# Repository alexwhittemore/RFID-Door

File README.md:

RFID Door Lock
==============

This project centers around a [Parallax RFID reader](http://www.parallax.com/tabid/768/ProductID/114/Default.aspx) and an Arduino for reading 125khz RFID tags as a means of authentication for opening a deadbolt. The main PCB holds the barebones Arduino-compatible clone, a socket for a Digi Xbee module for communication with a home automation network or a computer, and power circuitry. It has connectors for the RFID module, a standard hobby servo to actuate the deadbolt, and a magnetic reed switch to sense whether or not the door is presently closed. It also has a header which breaks out all power connections, such that external 5V and 3.3V sources can be used.

RFID Reader
-----------

The Parallax RFID Reader above from Grand Idea Studio and Parallax is used. Both SOUT and /ENABLE are connected to the Arduino, and it is intended that a software serial port will be used (since the hardware serial is used elsewhere for communication and programming). Given this configuration, the RFID header is pin-compatible with the [new RFID reader/writer from Parallax](http://www.parallax.com/Store/Accessories/CommunicationRF/tabid/161/ProductID/688/List/0/Default.aspx?SortField=ProductName,ProductName) should that be desired in the future.

Arduino
-------

A barebones Arduino is implemented with a PDIP AVR socket (ATMega8/168/328 compatible) and an external 16MHz crystal. Arduino pins 0,1 are used for a hardware UART connection to the Xbee module. Pins 2,3 are connected to RFID SOUT and /ENABLE, respectively, usable either as GPIO or software serial. Pin 5 is used to drive the servo motor signal. AD 0 is used to sense the door open magnetic reed switch. Pull up and pull down resistor footprints are included, to be populated in accordance with the use of a normally open or normally closed reed switch. 

Additionally, a reset switch and an ISP programming header are included for users who may wish to program the chip either without the Arduino environment or simply without removing the chip from the board.

Xbee
----

A socket is included for use with a Digi Xbee module. These should all be pin-compatible across series 1/2/pro units as well as 2.4GHz/900MHz, and only the power, reset, and serial pins are utilzed. Installing this optional module allows for remote programming (I think?) as well as communication with the rest of a home automation network or a central computer. Ideas for this feature are: dynamic updating of the access list, access logging, internet-based access interface (unlock the door from your smart phone!). A reset button for the Xbee is also implemented, as is necessary for remote updating.

Level Translation
-----------------

The Xbee module is 3.3v and the Arduino is 5v, so level translation on the UART lines is necessary. The method used in the Xbee shield for Arduino is a series 10kOhm resistor on the Arduino Tx/Xbee Rx line such that the ESD diodes in the Xbee aren't overwhelmed with 20mA out of the Arduino. There is no translation on the Xbee Tx/Arduino Rx, with the expectation that 3.3v will be sufficient for a logic 'High' on the Arduino. This scheme may be used for parts count/cost reduction by solder bridging SJ1 and populating R3.

Alternately, footprints are included for On Semi MC74VHC1GT126 level non-inverting buffers. These will accurately translate 3.3V inputs to 5V outputs and vice-versa, where any input 0-10V is acceptable and 'High' output = Vdd. Populate these and leave SJ1 and R3 unbridged/unpopulated for full level translation.

Finally, headers on both input and output sides of level translation are included for ease of debugging.

Power
-----

Regulators are included with appropriate bypassing for 5V and 3.3V supplies. They are cascaded - a Vin pin is provided to supply power to be regulated down to 5V, then the 3.3V regulator takes its input from this 5V line:

Vin->`7805 Regulator`--5V+USB-->`REG103`-->3.3V

Therefore, the 5V regulator may be populated, and simply won't be used if Vin isn't supplied. However, if both external 5V and 3.3V supplies are used, the 3.3V regulator MUST be unpopulated! A USB Mini-B connector is also provided to optionally supply 5V power. Note that there is NO protection of ANY kind - this is intended only for use with dumb wall chargers or CAREFUL use supplying power from a computer. That is, the 5v regulator MUST NOT have power to it, or there could be damage!

Additionally, a REG103 from Burr-Brown (TI) is used as the 3.3V regulator. It's not a conventional part in the hobbyist spectrum (It's not used by Sparkfun/Dangerous Prototypes/OpenPilot/anyone else) - I just happened to have some. But they're inexpensive and highly available on Digikey and Mouser.

Software
--------

I haven't written it yet. But if you get to it before I do, it's a pretty standard mishmash of the SoftwareSerial library, some demo code for the RFID reader, and standard UART for the Xbee.

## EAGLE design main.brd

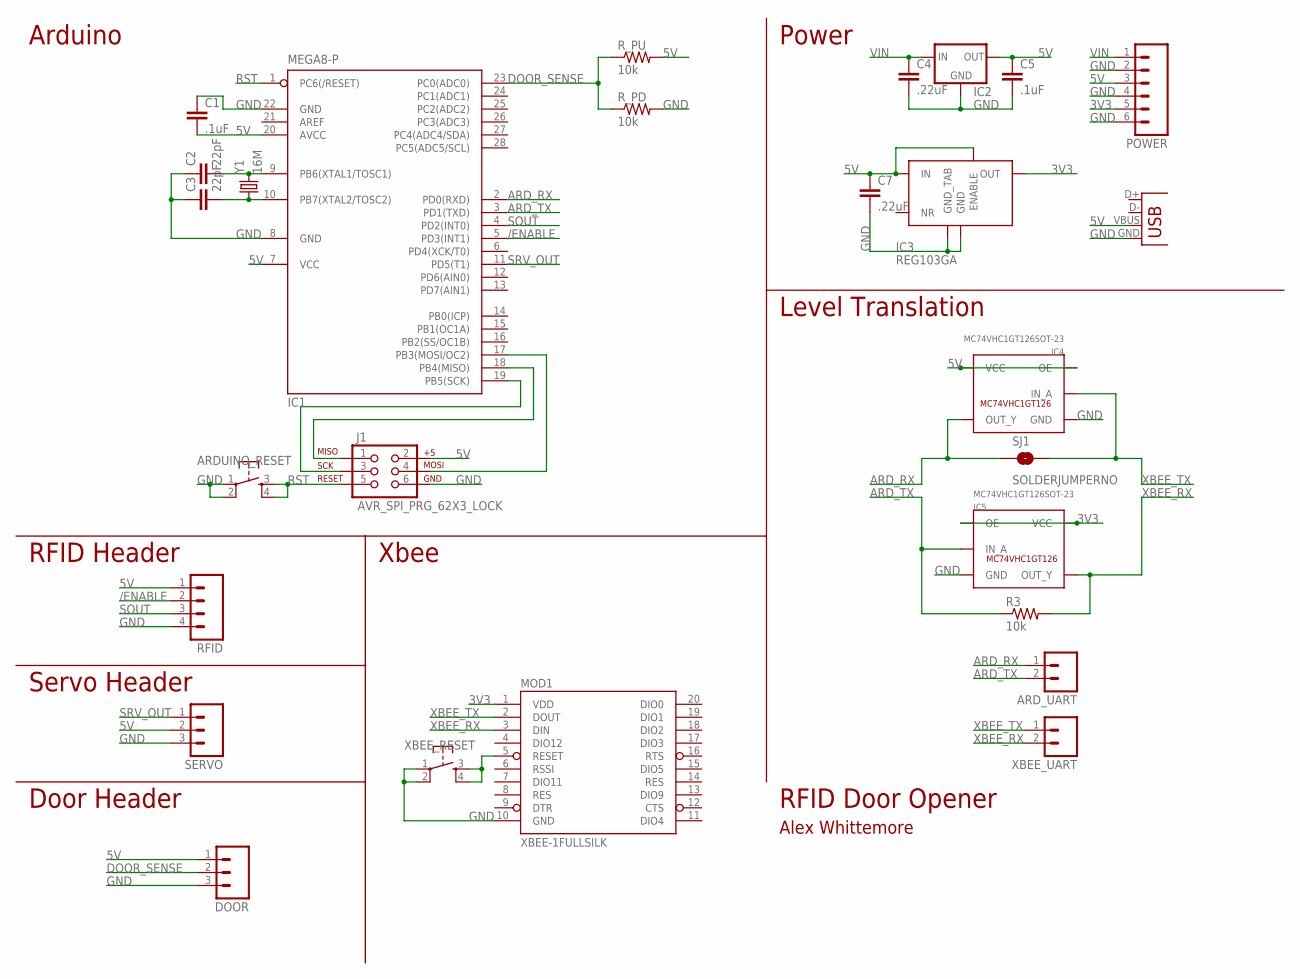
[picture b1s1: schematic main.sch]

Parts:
ARDUINO_RESET: TAC_SWITCHPTH; TACTILE-PTH
ARD_UART: M02LOCK_LONGPADS; 1X02_LOCK_LONGPADS
C1, C5: .1uF; 0805
C2, C3: 22pF; 0805
C4, C7: .22uF; 0805
DOOR: M03LOCK; 1X03_LOCK
IC1: MEGA8-P; DIL28-3
IC2: V_REG_78XX-TO-220; TO-220-ALT
IC3: REG103GA; SOT223-5
IC4, IC5: MC74VHC1GT126SOT-23; SOT23-5L
J1: AVR_SPI_PRG_62X3_LOCK; 2X3_LOCK
MOD1: XBEE-1FULLSILK; XBEE
POWER: M06LOCK; 1X06_LOCK
R3: 10k; 0805
RFID: M04LOCK_LONGPADS; 1X04_LOCK_LONGPADS
R_PD: 10k; 0805
R_PU: 10k; 0805
SERVO: M03LOCK; 1X03_LOCK
SJ1: SOLDERJUMPERNO; SJ_2S-NO
X1: USB-SMD-NS; USB-MINIB-NOSTOP
XBEE_RESET: TAC_SWITCHPTH; TACTILE-PTH
XBEE_UART: M02LOCK_LONGPADS; 1X02_LOCK_LONGPADS
Y1: 16M; HC49UP

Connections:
3V3: IC3.2 (OUT), IC5.1 (OE), IC5.5 (VCC), MOD1.1 (VDD), POWER.5
5V: C1.2, C5.1, C7.1, DOOR.1, IC1.7 (VCC), IC1.20 (AVCC), IC2.OUT, IC3.1 (IN), IC3.5 (ENABLE), IC4.1 (OE), IC4.5 (VCC), J1.2, POWER.3, RFID.1, R_PU.2, SERVO.2, X1.VBUS
/ENABLE: IC1.5 (PD3(INT1)), RFID.2
ARD_RX: ARD_UART.1, IC1.2 (PD0(RXD)), IC4.4 (OUT_Y), SJ1.1
ARD_TX: ARD_UART.2, IC1.3 (PD1(TXD)), IC5.2 (IN_A), R3.1
DOOR_SENSE: DOOR.2, IC1.23 (PC0(ADC0)), R_PD.1, R_PU.1
GND: ARDUINO_RESET.1, ARDUINO_RESET.2, C1.1, C2.1, C3.1, C4.2, C5.2, C7.2, DOOR.3, IC1.8 (GND), IC1.22 (GND), IC2.GND, IC3.3 (GND), IC3.TAB (GND_TAB), IC4.3 (GND), IC5.3 (GND), J1.6, MOD1.10 (GND), POWER.2, POWER.4, POWER.6, RFID.4, R_PD.2, SERVO.3, X1.GND, XBEE_RESET.1, XBEE_RESET.2
ISP_MISO: IC1.18 (PB4(MISO)), J1.1
ISP_MOSI: IC1.17 (PB3(MOSI/OC2)), J1.4
ISP_SCK: IC1.19 (PB5(SCK)), J1.3
unnamed: C2.2, IC1.9 (PB6(XTAL1/TOSC1)), Y1.2
unnamed: C3.2, IC1.10 (PB7(XTAL2/TOSC2)), Y1.1
RST: ARDUINO_RESET.3, ARDUINO_RESET.4, IC1.1 (PC6(/RESET)), J1.5
SOUT: IC1.4 (PD2(INT0)), RFID.3
SRV_OUT: IC1.11 (PD5(T1)), SERVO.1
VIN: C4.1, IC2.IN, POWER.1
XBEE_RST: MOD1.5 (RESET), XBEE_RESET.3, XBEE_RESET.4
XBEE_RX: IC5.4 (OUT_Y), MOD1.3 (DIN), R3.2, XBEE_UART.2
XBEE_TX: IC4.2 (IN_A), MOD1.2 (DOUT), SJ1.2, XBEE_UART.1

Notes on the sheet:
Level Translation
Power
Arduino
Xbee
RFID Header
Servo Header
Door Header
RFID Door Opener
Alex Whittemore

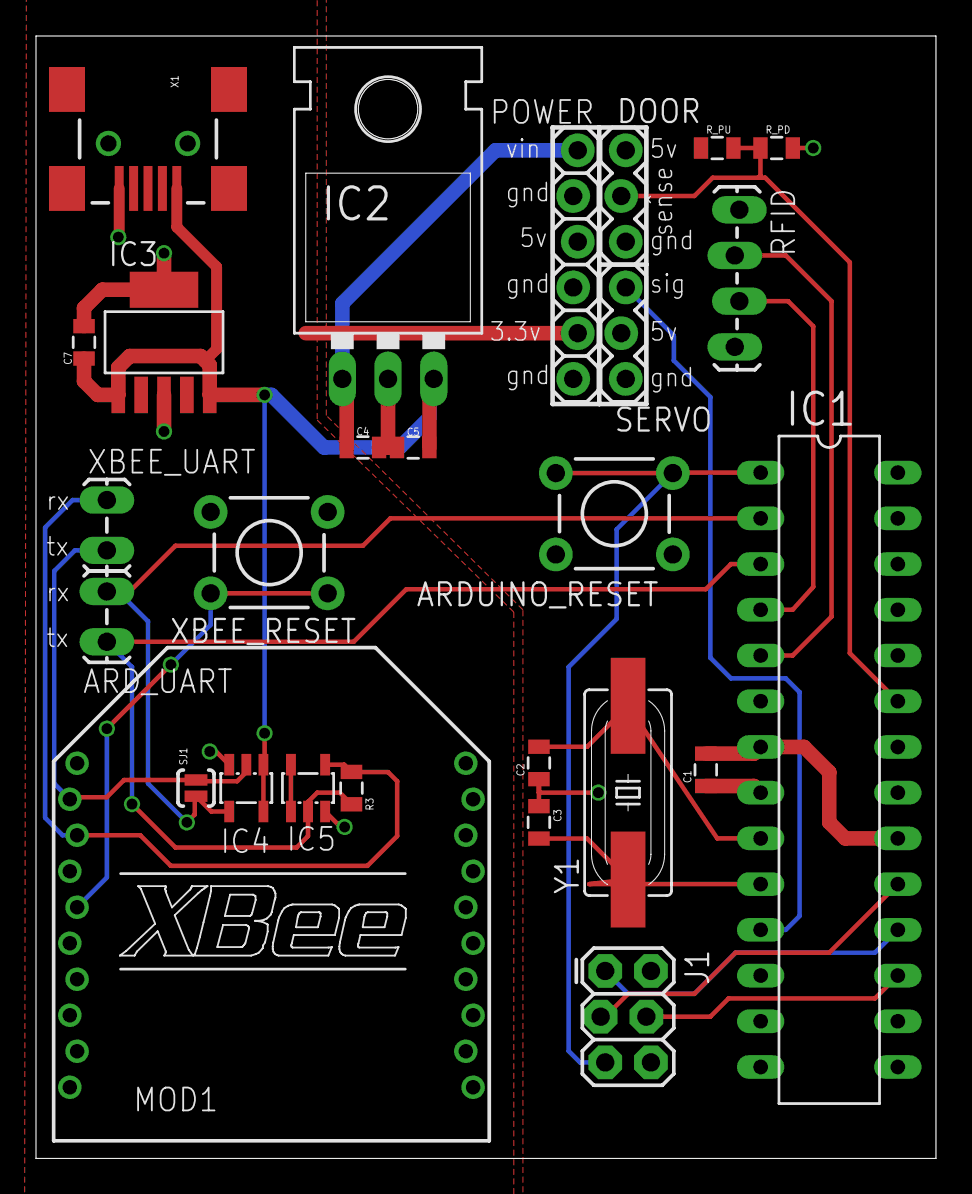
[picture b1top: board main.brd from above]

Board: 2 copper layers, 50.0 x 62.4 mm, 27 parts (0 on the bottom side), 19 nets.

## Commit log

2011-11-30 Initial Commit
    Included is a more-or-less complete schematic, a preliminary board
    layout, and a readme to describe the project on Github.
2011-12-01 Significantly reduced layout size to fit within 10x5cm
    Minor schematic modifications to support small board layout, large
    board modifications. TODO: Lots of silk screen clean up.
2011-12-19 Converted to new Eagle V6 XML format
2013-06-20 Ignore eagle.epf
